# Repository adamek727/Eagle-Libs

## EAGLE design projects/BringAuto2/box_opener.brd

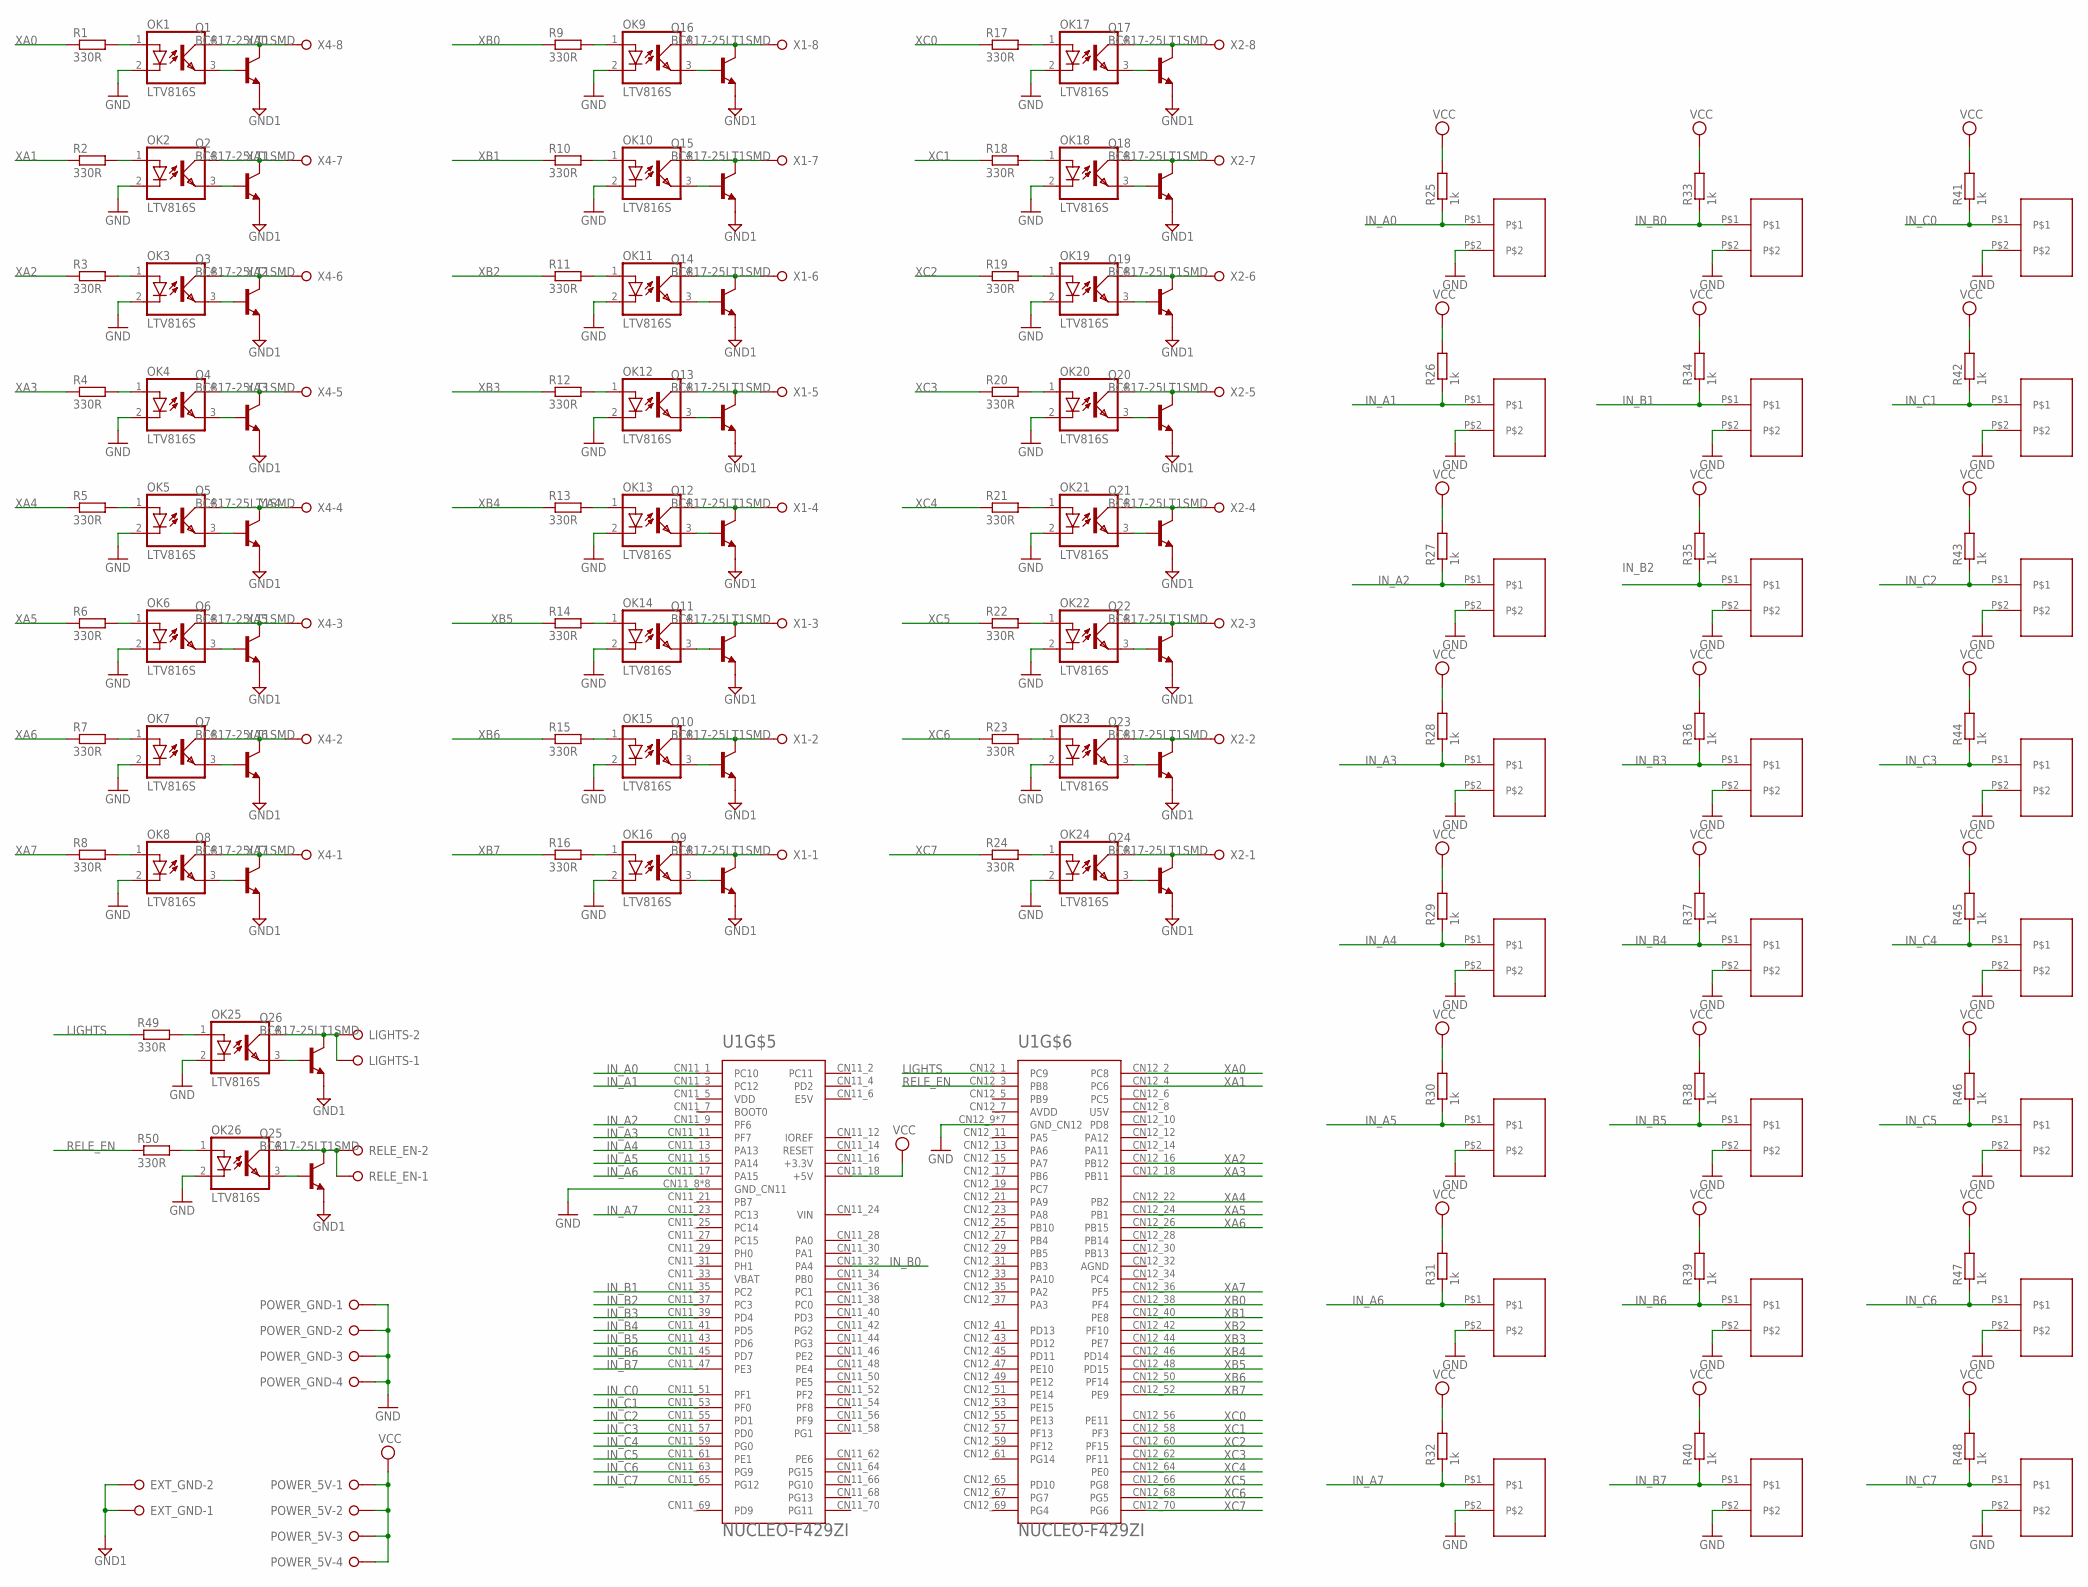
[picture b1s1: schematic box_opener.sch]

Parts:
EXT_GND: W237-02P; W237-132
LIGHTS: W237-132
OK1, OK2, OK3, OK4, OK5, OK6, OK7, OK8, OK9, OK10, OK11, OK12, OK13, OK14, OK15, OK16, OK17, OK18, OK19, OK20, OK21, OK22, OK23, OK24, OK25, OK26: LTV816S; DIL4-SMD
POWER_5V: W237-4P
POWER_GND: W237-4P
Q1, Q2, Q3, Q4, Q5, Q6, Q7, Q8, Q9, Q10, Q11, Q12, Q13, Q14, Q15, Q16, Q17, Q18, Q19, Q20, Q21, Q22, Q23, Q24, Q25, Q26: BC817-25LT1SMD; SOT23-BEC
R1, R2, R3, R4, R5, R6, R7, R8, R9, R10, R11, R12, R13, R14, R15, R16, R17, R18, R19, R20, R21, R22, R23, R24, R49, R50: 330R; M1206
R25, R26, R27, R28, R29, R30, R31, R32, R33, R34, R35, R36, R37, R38, R39, R40, R41, R42, R43, R44, R45, R46, R47, R48: 1k; M1206
RELE_EN: W237-132
U1: NUCLEO-F429ZI; MODULE_NUCLEO-F429ZI
U$1, U$2, U$3, U$4, U$5, U$6, U$7, U$8, U$9, U$10, U$11, U$12, U$13, U$14, U$15, U$16, U$17, U$18, U$19, U$20, U$21, U$22, U$23, U$24: PSH04-02
X1, X2, X4: W237-8P

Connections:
GND: OK1.2 (C), OK2.2 (C), OK3.2 (C), OK4.2 (C), OK5.2 (C), OK6.2 (C), OK7.2 (C), OK8.2 (C), OK9.2 (C), OK10.2 (C), OK11.2 (C), OK12.2 (C), OK13.2 (C), OK14.2 (C), OK15.2 (C), OK16.2 (C), OK17.2 (C), OK18.2 (C), OK19.2 (C), OK20.2 (C), OK21.2 (C), OK22.2 (C), OK23.2 (C), OK24.2 (C), OK25.2 (C), OK26.2 (C), POWER_GND.1, POWER_GND.2, POWER_GND.3, POWER_GND.4, U1.CN11_8 (GND_CN11), U1.CN11_19 (GND_CN11), U1.CN11_20 (GND_CN11), U1.CN11_22 (GND_CN11), U1.CN11_49 (GND_CN11), U1.CN11_60 (GND_CN11), U1.CN11_71 (GND_CN11), U1.CN11_72 (GND_CN11), U1.CN12_9 (GND_CN12), U1.CN12_20 (GND_CN12), U1.CN12_39 (GND_CN12), U1.CN12_54 (GND_CN12), U1.CN12_63 (GND_CN12), U1.CN12_71 (GND_CN12), U1.CN12_72 (GND_CN12), U$1.P$2, U$2.P$2, U$3.P$2, U$4.P$2, U$5.P$2, U$6.P$2, U$7.P$2, U$8.P$2, U$9.P$2, U$10.P$2, U$11.P$2, U$12.P$2, U$13.P$2, U$14.P$2, U$15.P$2, U$16.P$2, U$17.P$2, U$18.P$2, U$19.P$2, U$20.P$2, U$21.P$2, U$22.P$2, U$23.P$2, U$24.P$2
GND1: EXT_GND.1, EXT_GND.2, Q1.E, Q2.E, Q3.E, Q4.E, Q5.E, Q6.E, Q7.E, Q8.E, Q9.E, Q10.E, Q11.E, Q12.E, Q13.E, Q14.E, Q15.E, Q16.E, Q17.E, Q18.E, Q19.E, Q20.E, Q21.E, Q22.E, Q23.E, Q24.E, Q25.E, Q26.E
IN_A0: R25.1, U1.CN11_1 (PC10), U$1.P$1
IN_A1: R26.1, U1.CN11_3 (PC12), U$2.P$1
IN_A2: R27.1, U1.CN11_9 (PF6), U$3.P$1
IN_A3: R28.1, U1.CN11_11 (PF7), U$4.P$1
IN_A4: R29.1, U1.CN11_13 (PA13), U$5.P$1
IN_A5: R30.1, U1.CN11_15 (PA14), U$6.P$1
IN_A6: R31.1, U1.CN11_17 (PA15), U$7.P$1
IN_A7: R32.1, U1.CN11_23 (PC13), U$8.P$1
IN_B0: R33.1, U1.CN11_32 (PA4), U$9.P$1
IN_B1: R34.1, U1.CN11_35 (PC2), U$10.P$1
IN_B2: R35.1, U1.CN11_37 (PC3), U$11.P$1
IN_B3: R36.1, U1.CN11_39 (PD4), U$12.P$1
IN_B4: R37.1, U1.CN11_41 (PD5), U$13.P$1
IN_B5: R38.1, U1.CN11_43 (PD6), U$14.P$1
IN_B6: R39.1, U1.CN11_45 (PD7), U$15.P$1
IN_B7: R40.1, U1.CN11_47 (PE3), U$16.P$1
IN_C0: R41.1, U1.CN11_51 (PF1), U$17.P$1
IN_C1: R42.1, U1.CN11_53 (PF0), U$18.P$1
IN_C2: R43.1, U1.CN11_55 (PD1), U$19.P$1
IN_C3: R44.1, U1.CN11_57 (PD0), U$20.P$1
IN_C4: R45.1, U1.CN11_59 (PG0), U$21.P$1
IN_C5: R46.1, U1.CN11_61 (PE1), U$22.P$1
IN_C6: R47.1, U1.CN11_63 (PG9), U$23.P$1
IN_C7: R48.1, U1.CN11_65 (PG12), U$24.P$1
LIGHTS: R49.1, U1.CN12_1 (PC9)
unnamed: OK1.1 (A), R1.2
unnamed: OK9.1 (A), R9.2
unnamed: OK2.1 (A), R2.2
unnamed: OK10.1 (A), R10.2
unnamed: OK11.1 (A), R11.2
unnamed: OK12.1 (A), R12.2
unnamed: OK3.1 (A), R3.2
unnamed: OK13.1 (A), R13.2
unnamed: OK14.1 (A), R14.2
unnamed: OK4.1 (A), R4.2
unnamed: OK15.1 (A), R15.2
unnamed: OK16.1 (A), R16.2
unnamed: OK5.1 (A), R5.2
unnamed: OK17.1 (A), R17.2
unnamed: OK18.1 (A), R18.2
unnamed: OK6.1 (A), R6.2
unnamed: OK19.1 (A), R19.2
unnamed: OK20.1 (A), R20.2
unnamed: OK7.1 (A), R7.2
unnamed: OK21.1 (A), R21.2
unnamed: OK22.1 (A), R22.2
unnamed: OK8.1 (A), R8.2
unnamed: OK23.1 (A), R23.2
unnamed: OK24.1 (A), R24.2
unnamed: OK25.1 (A), R49.2
unnamed: OK26.1 (A), R50.2
unnamed: OK26.4 (COL), Q25.C, RELE_EN.1, RELE_EN.2
unnamed: LIGHTS.1, LIGHTS.2, OK25.4 (COL), Q26.C
unnamed: OK2.3 (EMIT), Q2.B
unnamed: OK1.3 (EMIT), Q1.B
unnamed: OK3.3 (EMIT), Q3.B
unnamed: OK4.3 (EMIT), Q4.B
unnamed: OK16.4 (COL), Q9.C, X1.1
unnamed: OK15.4 (COL), Q10.C, X1.2
unnamed: OK14.4 (COL), Q11.C, X1.3
unnamed: OK13.4 (COL), Q12.C, X1.4
unnamed: OK12.4 (COL), Q13.C, X1.5
unnamed: OK11.4 (COL), Q14.C, X1.6
unnamed: OK10.4 (COL), Q15.C, X1.7
unnamed: OK9.4 (COL), Q16.C, X1.8
unnamed: OK17.4 (COL), Q17.C, X2.8
unnamed: OK18.4 (COL), Q18.C, X2.7
unnamed: OK19.4 (COL), Q19.C, X2.6
unnamed: OK20.4 (COL), Q20.C, X2.5
unnamed: OK21.4 (COL), Q21.C, X2.4
unnamed: OK22.4 (COL), Q22.C, X2.3
unnamed: OK23.4 (COL), Q23.C, X2.2
unnamed: OK24.4 (COL), Q24.C, X2.1
unnamed: OK5.3 (EMIT), Q5.B
unnamed: OK6.3 (EMIT), Q6.B
unnamed: OK7.3 (EMIT), Q7.B
unnamed: OK8.3 (EMIT), Q8.B
unnamed: OK16.3 (EMIT), Q9.B
unnamed: OK15.3 (EMIT), Q10.B
unnamed: OK13.3 (EMIT), Q12.B
unnamed: OK14.3 (EMIT), Q11.B
unnamed: OK12.3 (EMIT), Q13.B
unnamed: OK11.3 (EMIT), Q14.B
unnamed: OK10.3 (EMIT), Q15.B
unnamed: OK9.3 (EMIT), Q16.B
unnamed: OK17.3 (EMIT), Q17.B
unnamed: OK18.3 (EMIT), Q18.B
unnamed: OK19.3 (EMIT), Q19.B
unnamed: OK20.3 (EMIT), Q20.B
unnamed: OK21.3 (EMIT), Q21.B
unnamed: OK22.3 (EMIT), Q22.B
unnamed: OK23.3 (EMIT), Q23.B
unnamed: OK24.3 (EMIT), Q24.B
unnamed: OK26.3 (EMIT), Q25.B
unnamed: OK25.3 (EMIT), Q26.B
RELE_EN: R50.1, U1.CN12_3 (PB8)
VCC: POWER_5V.1, POWER_5V.2, POWER_5V.3, POWER_5V.4, R25.2, R26.2, R27.2, R28.2, R29.2, R30.2, R31.2, R32.2, R33.2, R34.2, R35.2, R36.2, R37.2, R38.2, R39.2, R40.2, R41.2, R42.2, R43.2, R44.2, R45.2, R46.2, R47.2, R48.2, U1.CN11_18 (+5V)
XA0: R1.1, U1.CN12_2 (PC8)
XA1: R2.1, U1.CN12_4 (PC6)
XA2: R3.1, U1.CN12_16 (PB12)
XA3: R4.1, U1.CN12_18 (PB11)
XA4: R5.1, U1.CN12_22 (PB2)
XA5: R6.1, U1.CN12_24 (PB1)
XA6: R7.1, U1.CN12_26 (PB15)
XA7: R8.1, U1.CN12_36 (PF5)
XB0: R9.1, U1.CN12_38 (PF4)
XB1: R10.1, U1.CN12_40 (PE8)
XB2: R11.1, U1.CN12_42 (PF10)
XB3: R12.1, U1.CN12_44 (PE7)
XB4: R13.1, U1.CN12_46 (PD14)
XB5: R14.1, U1.CN12_48 (PD15)
XB6: R15.1, U1.CN12_50 (PF14)
XB7: R16.1, U1.CN12_52 (PE9)
XC0: R17.1, U1.CN12_56 (PE11)
XC1: R18.1, U1.CN12_58 (PF3)
XC2: R19.1, U1.CN12_60 (PF15)
XC3: R20.1, U1.CN12_62 (PF11)
XC4: R21.1, U1.CN12_64 (PE0)
XC5: R22.1, U1.CN12_66 (PG8)
XC6: R23.1, U1.CN12_68 (PG5)
XC7: R24.1, U1.CN12_70 (PG6)
YA0: OK1.4 (COL), Q1.C, X4.8
YA1: OK2.4 (COL), Q2.C, X4.7
YA2: OK3.4 (COL), Q3.C, X4.6
YA3: OK4.4 (COL), Q4.C, X4.5
YA4: OK5.4 (COL), Q5.C, X4.4
YA5: OK6.4 (COL), Q6.C, X4.3
YA6: OK7.4 (COL), Q7.C, X4.2
YA7: OK8.4 (COL), Q8.C, X4.1

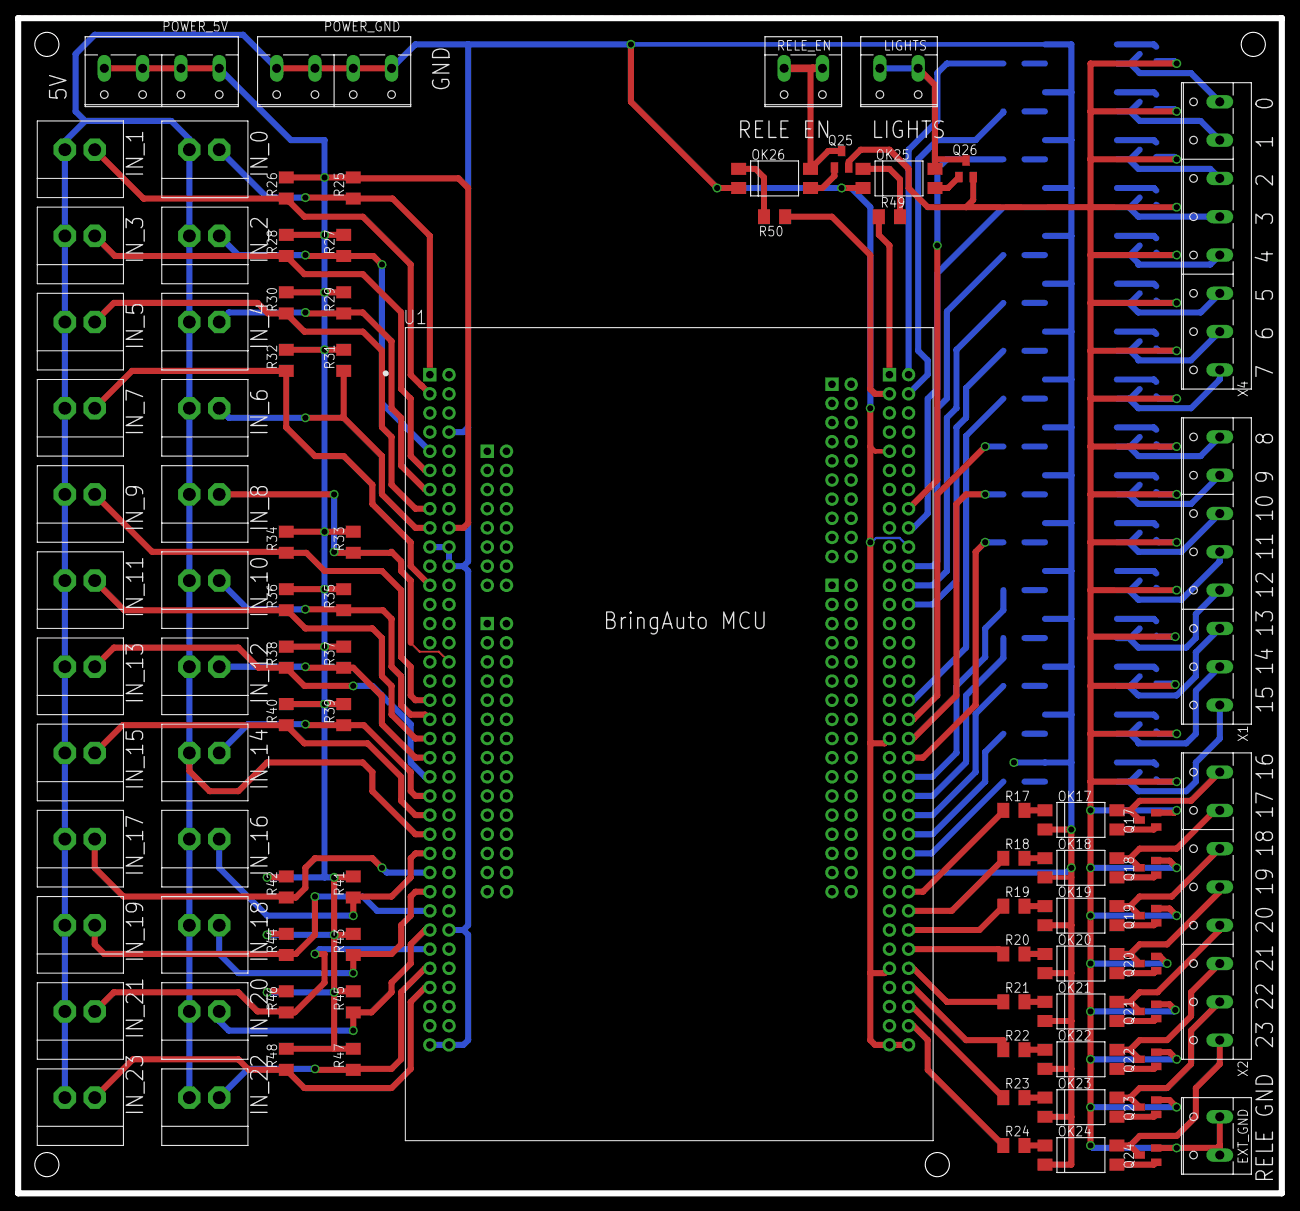
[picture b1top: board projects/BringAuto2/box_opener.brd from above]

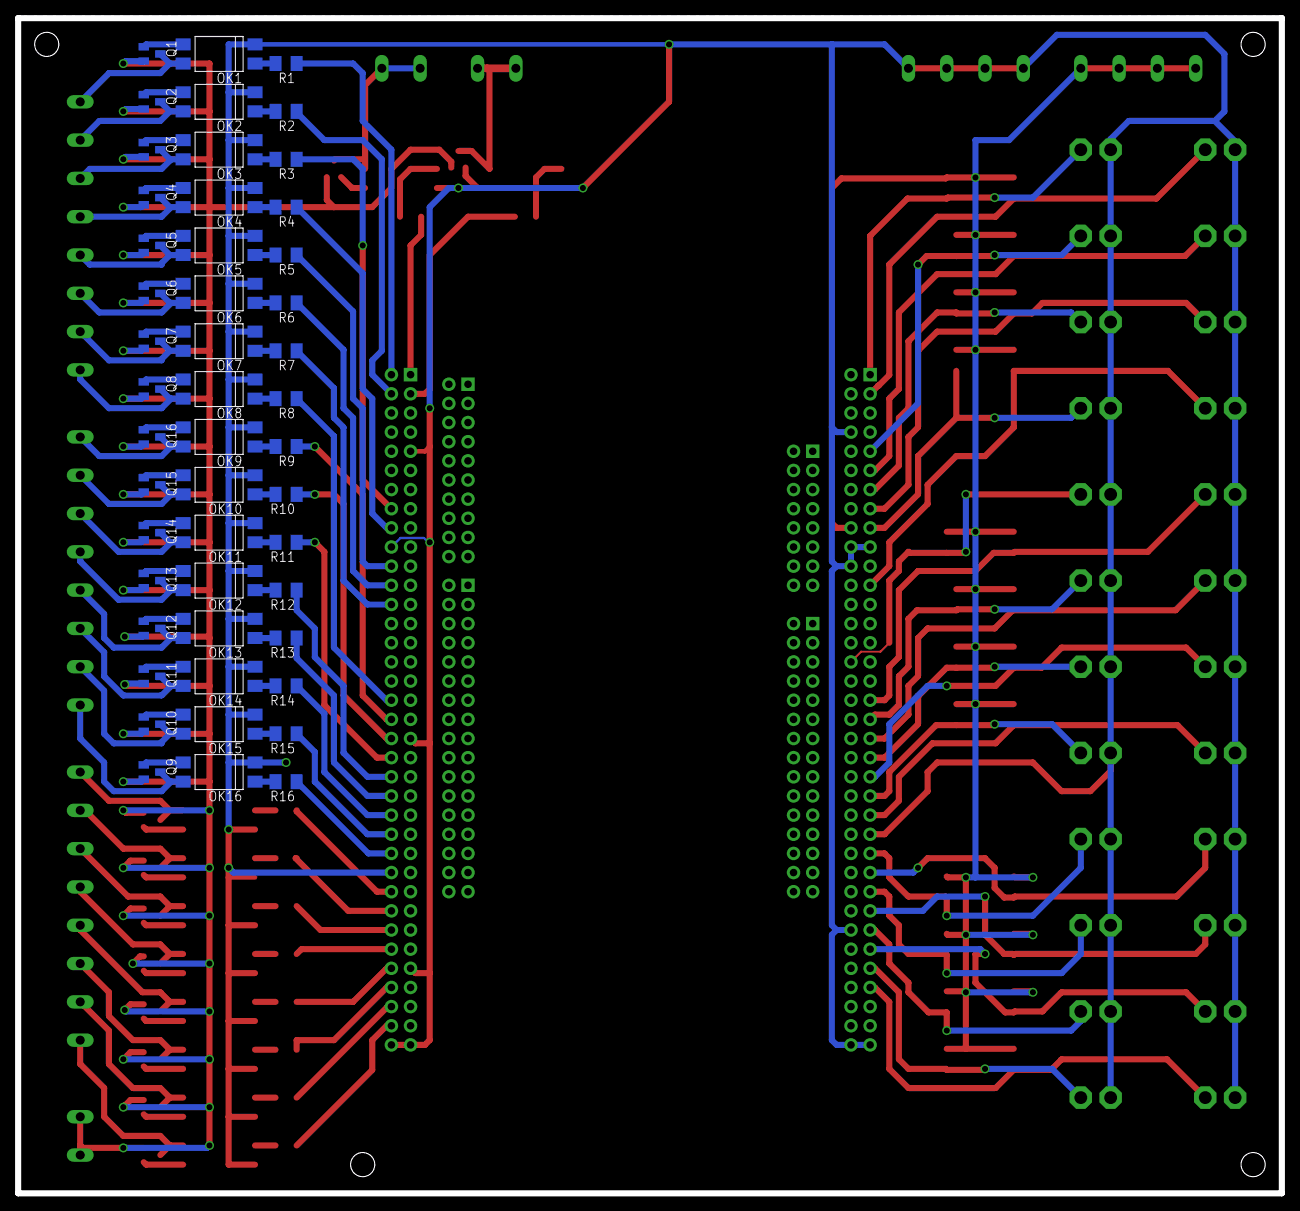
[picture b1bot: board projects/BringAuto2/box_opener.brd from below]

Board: 2 copper layers, 167.6 x 155.9 mm, 135 parts (48 on the bottom side), 131 nets.

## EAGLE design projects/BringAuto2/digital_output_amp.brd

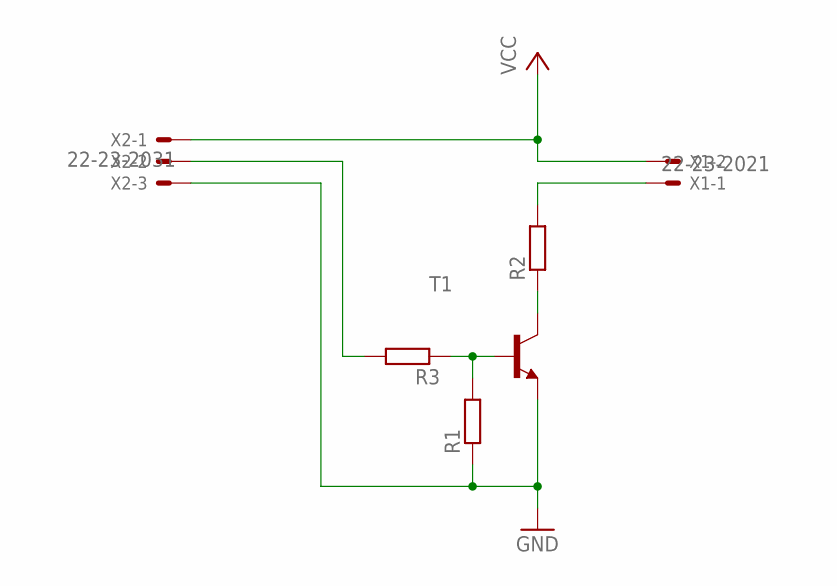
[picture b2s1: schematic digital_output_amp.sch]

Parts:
R1, R2, R3: R-EU_M1206; M1206
T1: BC817-40-NPN-SOT23-BEC; SOT23-BEC
X1: 22-23-2021
X2: 22-23-2031

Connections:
GND: R1.1, T1.E, X2.3
unnamed: R2.2, X1.1
unnamed: R2.1, T1.C
unnamed: R1.2, R3.1, T1.B
unnamed: R3.2, X2.2
VCC: X1.2, X2.1

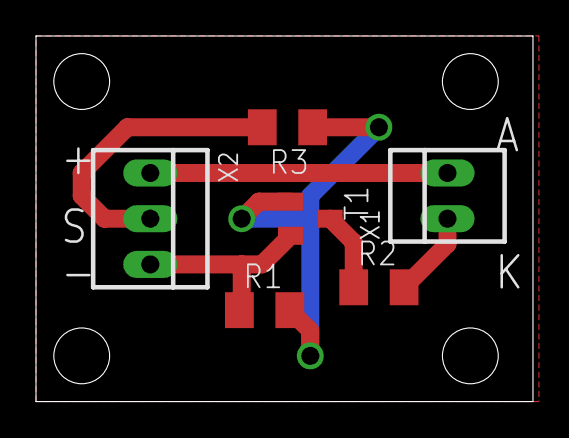
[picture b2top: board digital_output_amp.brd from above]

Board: 2 copper layers, 27.6 x 20.3 mm, 6 parts (0 on the bottom side), 6 nets.

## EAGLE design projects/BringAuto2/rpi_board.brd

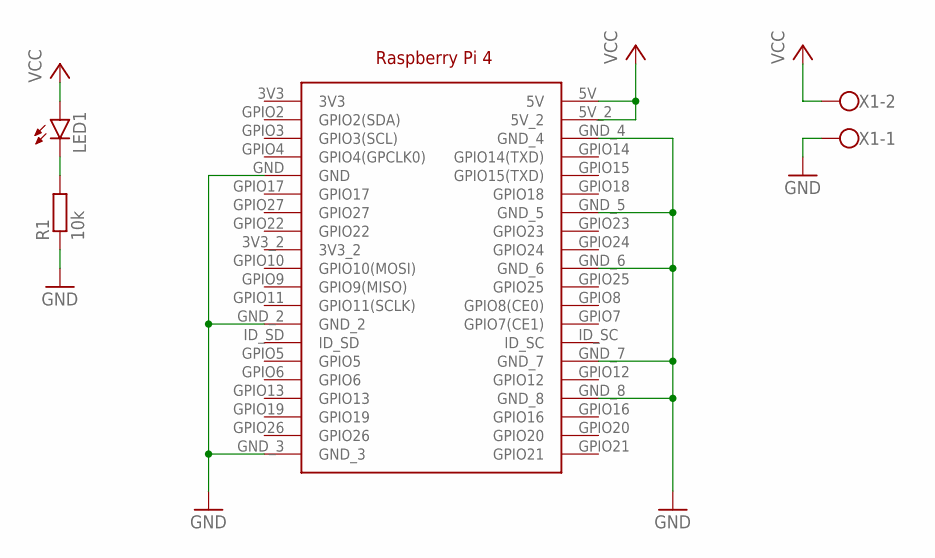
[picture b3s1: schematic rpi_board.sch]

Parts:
LED1: LEDSMT1206; 1206
R1: 10k; M1206
U$1: RPI_4; RPI4_FOOTPRINT
X1: W237-102

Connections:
GND: R1.1, U$1.GND, U$1.GND_2, U$1.GND_3, U$1.GND_4, U$1.GND_5, U$1.GND_6, U$1.GND_7, U$1.GND_8, X1.1
unnamed: LED1.C, R1.2
VCC: LED1.A, U$1.5V, U$1.5V_2, X1.2

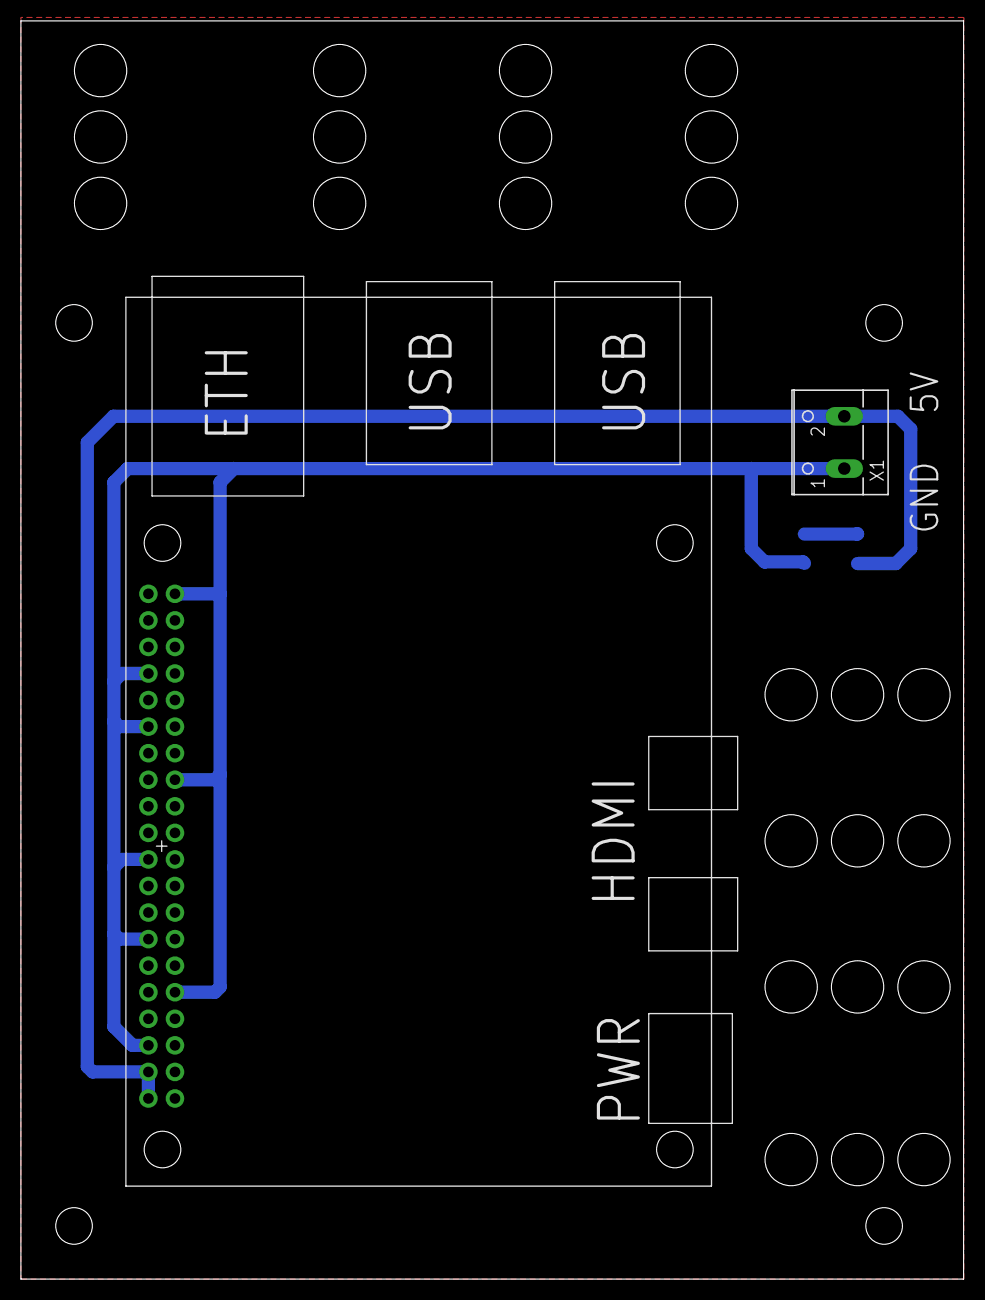
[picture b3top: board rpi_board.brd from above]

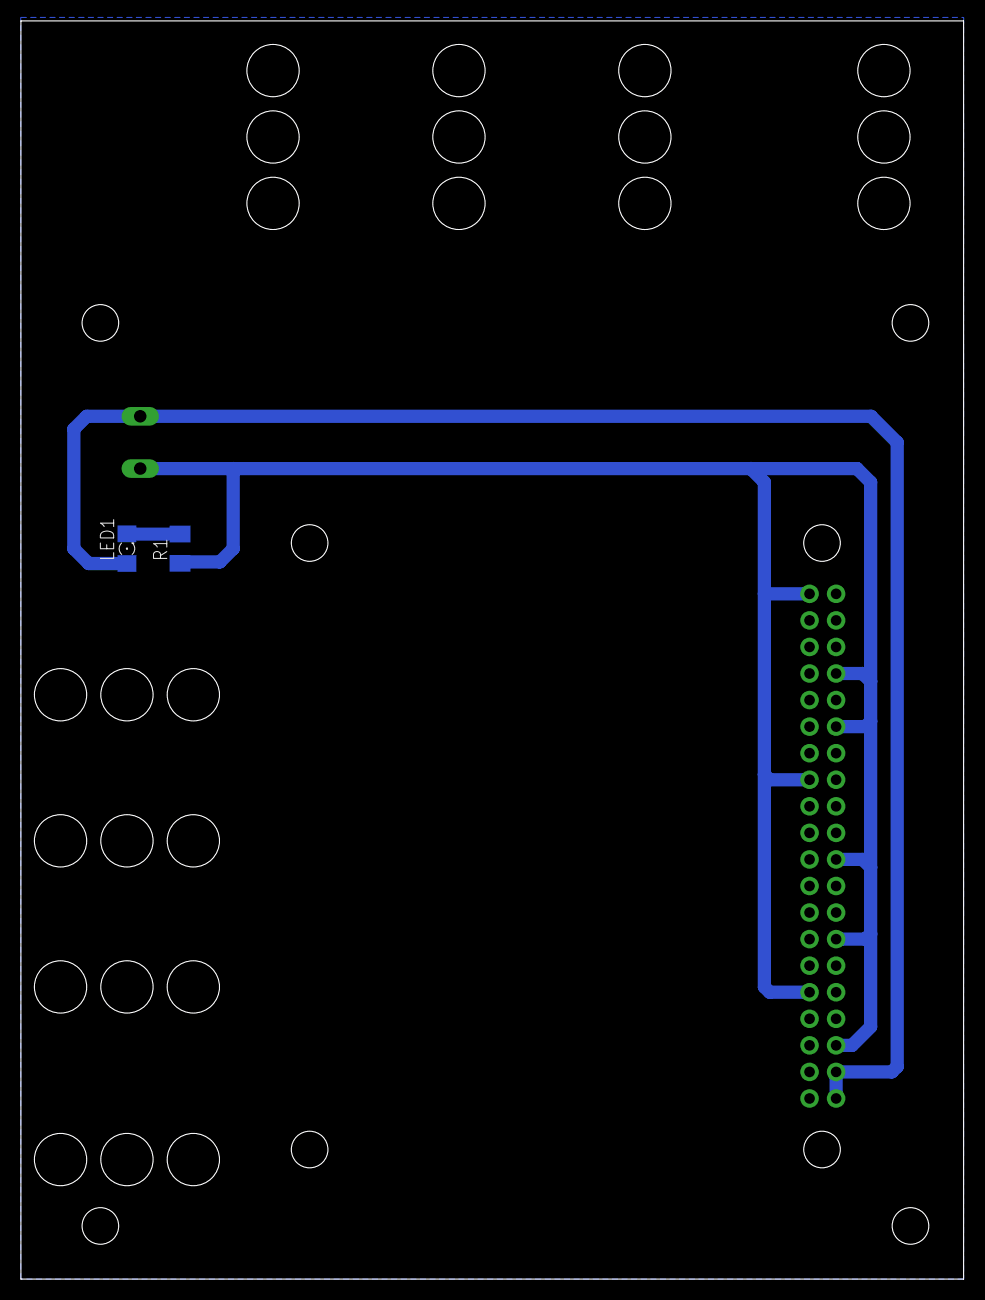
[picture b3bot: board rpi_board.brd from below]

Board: 2 copper layers, 90.2 x 120.3 mm, 4 parts (2 on the bottom side), 3 nets.

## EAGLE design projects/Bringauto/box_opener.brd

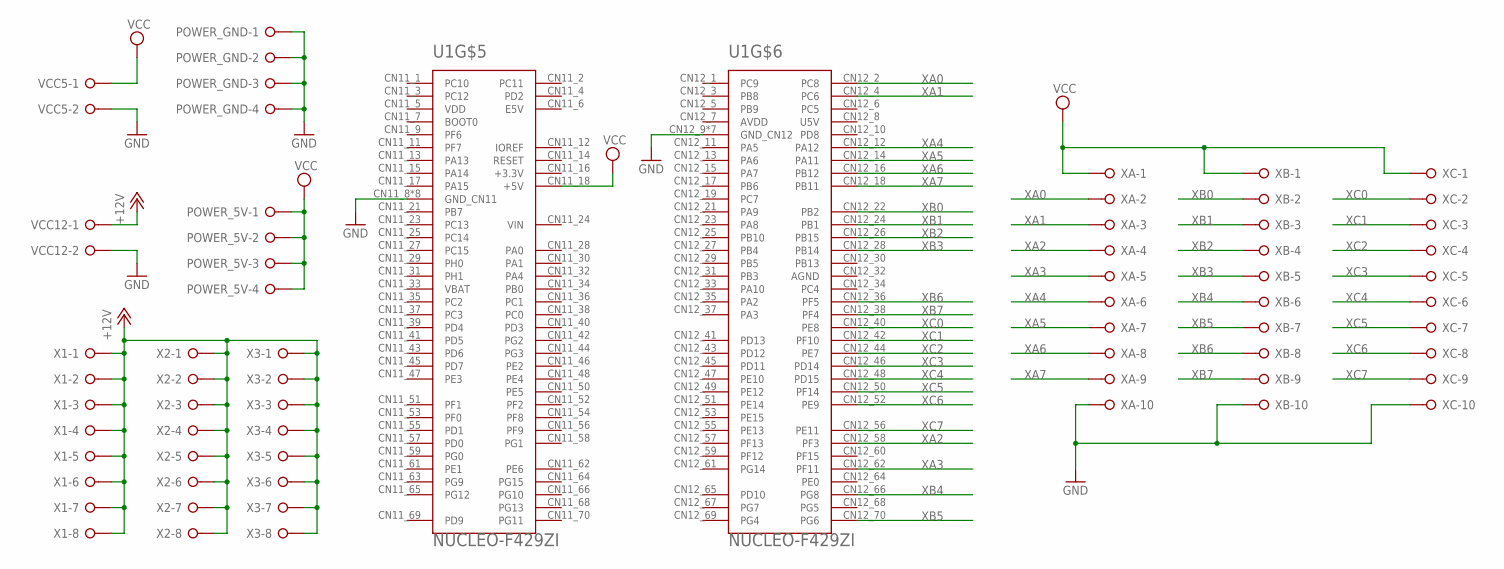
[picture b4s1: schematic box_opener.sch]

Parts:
POWER_5V: W237-4P
POWER_GND: W237-4P
U1: NUCLEO-F429ZI; MODULE_NUCLEO-F429ZI
VCC5, VCC12: W237-132
X1, X2, X3: W237-8P
XA: W237-10P
XB: W237-10P
XC: W237-10P

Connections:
+12V: VCC12.1, X1.1, X1.2, X1.3, X1.4, X1.5, X1.6, X1.7, X1.8, X2.1, X2.2, X2.3, X2.4, X2.5, X2.6, X2.7, X2.8, X3.1, X3.2, X3.3, X3.4, X3.5, X3.6, X3.7, X3.8
GND: POWER_GND.1, POWER_GND.2, POWER_GND.3, POWER_GND.4, U1.CN11_8 (GND_CN11), U1.CN11_19 (GND_CN11), U1.CN11_20 (GND_CN11), U1.CN11_22 (GND_CN11), U1.CN11_49 (GND_CN11), U1.CN11_60 (GND_CN11), U1.CN11_71 (GND_CN11), U1.CN11_72 (GND_CN11), U1.CN12_9 (GND_CN12), U1.CN12_20 (GND_CN12), U1.CN12_39 (GND_CN12), U1.CN12_54 (GND_CN12), U1.CN12_63 (GND_CN12), U1.CN12_71 (GND_CN12), U1.CN12_72 (GND_CN12), VCC5.2, VCC12.2, XA.10, XB.10, XC.10
VCC: POWER_5V.1, POWER_5V.2, POWER_5V.3, POWER_5V.4, U1.CN11_18 (+5V), VCC5.1, XA.1, XB.1, XC.1
XA0: U1.CN12_2 (PC8), XA.2
XA1: U1.CN12_4 (PC6), XA.3
XA2: U1.CN12_58 (PF3), XA.4
XA3: U1.CN12_62 (PF11), XA.5
XA4: U1.CN12_12 (PA12), XA.6
XA5: U1.CN12_14 (PA11), XA.7
XA6: U1.CN12_16 (PB12), XA.8
XA7: U1.CN12_18 (PB11), XA.9
XB0: U1.CN12_22 (PB2), XB.2
XB1: U1.CN12_24 (PB1), XB.3
XB2: U1.CN12_26 (PB15), XB.4
XB3: U1.CN12_28 (PB14), XB.5
XB4: U1.CN12_66 (PG8), XB.6
XB5: U1.CN12_70 (PG6), XB.7
XB6: U1.CN12_36 (PF5), XB.8
XB7: U1.CN12_38 (PF4), XB.9
XC0: U1.CN12_40 (PE8), XC.2
XC1: U1.CN12_42 (PF10), XC.3
XC2: U1.CN12_44 (PE7), XC.4
XC3: U1.CN12_46 (PD14), XC.5
XC4: U1.CN12_48 (PD15), XC.6
XC5: U1.CN12_50 (PF14), XC.7
XC6: U1.CN12_52 (PE9), XC.8
XC7: U1.CN12_56 (PE11), XC.9

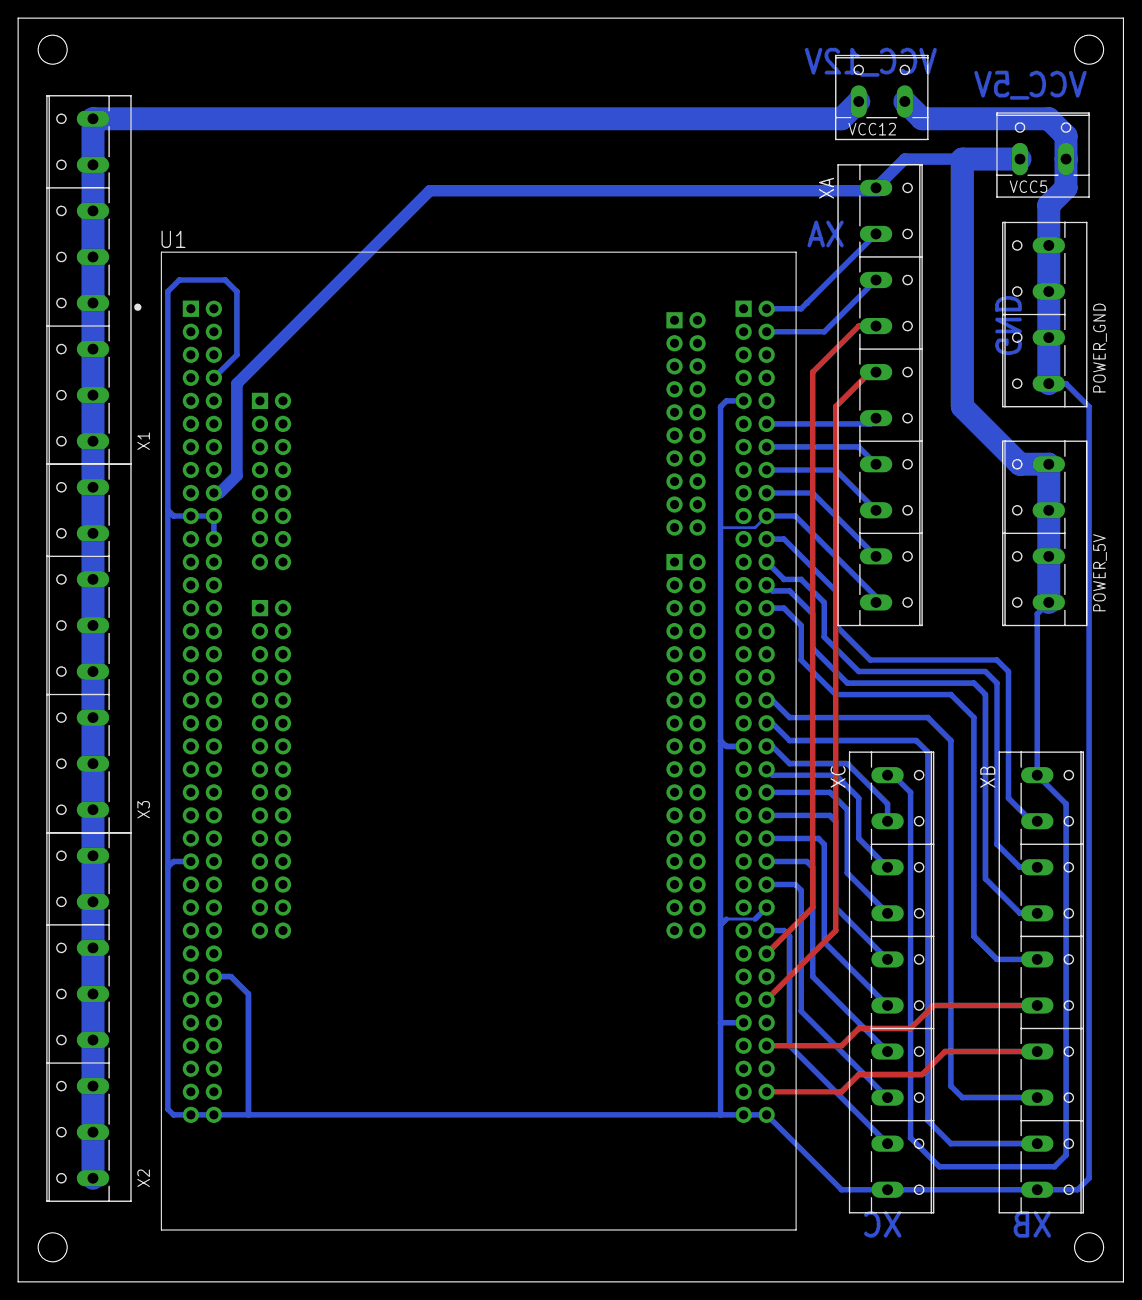
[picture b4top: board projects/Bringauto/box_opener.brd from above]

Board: 2 copper layers, 121.9 x 139.4 mm, 11 parts (0 on the bottom side), 27 nets.

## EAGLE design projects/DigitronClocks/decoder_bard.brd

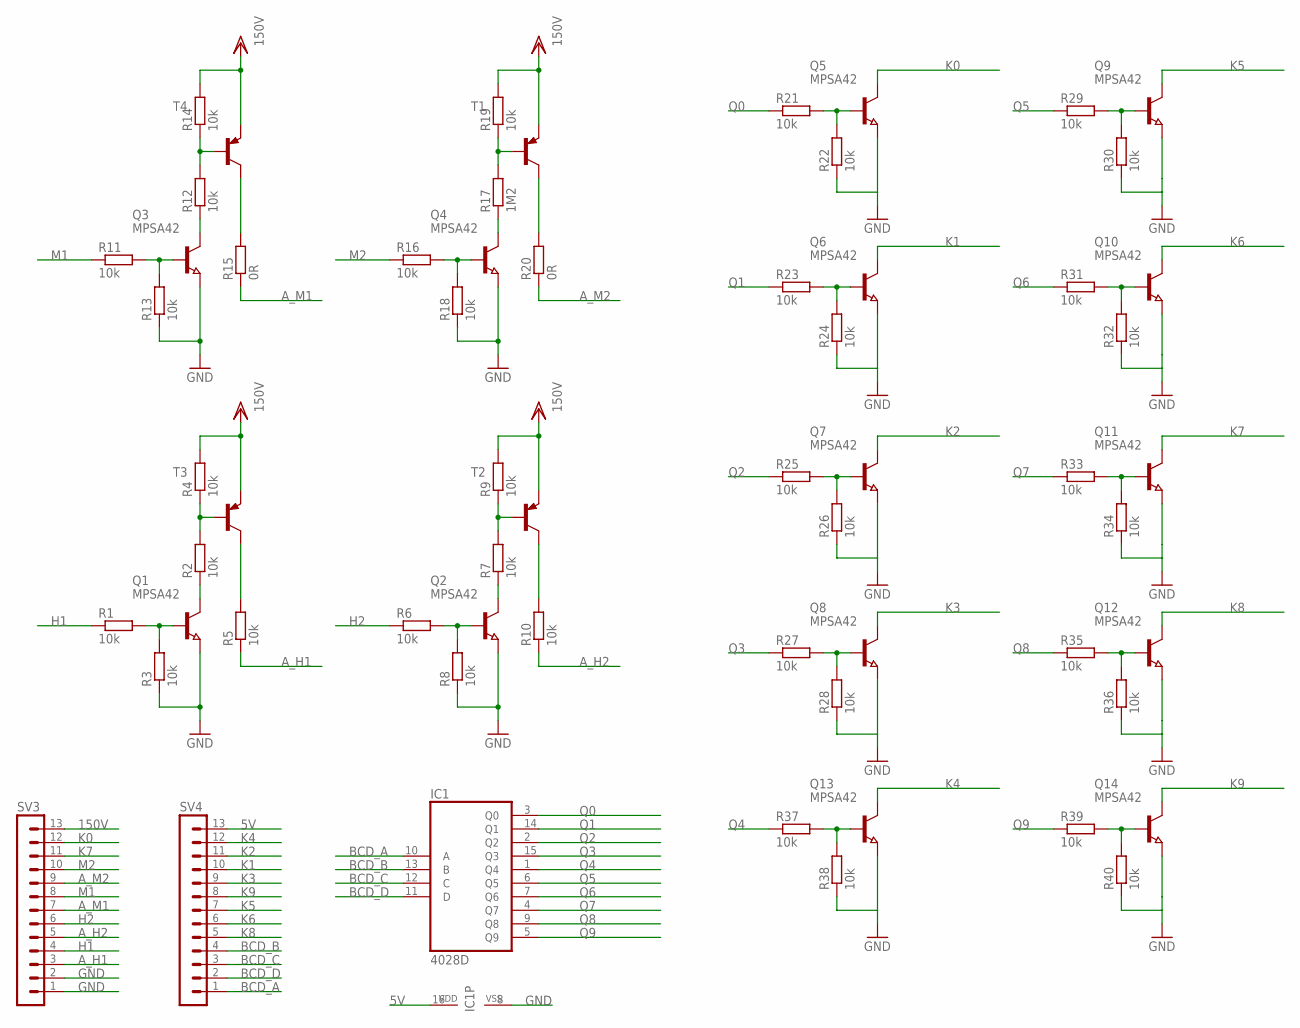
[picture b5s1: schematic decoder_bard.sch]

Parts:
IC1: 4028D; SO16
Q1, Q2, Q3, Q4, Q5, Q6, Q7, Q8, Q9, Q10, Q11, Q12, Q13, Q14: MPSA42; SOT23
R1, R2, R3, R4, R5, R6, R7, R8, R9, R10, R11, R12, R13, R14, R16, R18, R19, R21, R22, R23, R24, R25, R26, R27, R28, R29, R30, R31, R32, R33, R34, R35, R36, R37, R38, R39, R40: 10k; R1206
R15, R20: 0R; R1206
R17: 1M2; R1206
SV3, SV4: MA13-1
T1, T2, T3, T4: MMBTA92LT1-PNP-SOT23-BEC; SOT23-BEC

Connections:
5V: IC1.16 (VDD), SV4.13
150V: R4.2, R9.2, R14.2, R19.2, SV3.13, T1.E, T2.E, T3.E, T4.E
A_H1: R5.1, SV3.3
A_H2: R10.1, SV3.5
A_M1: R15.1, SV3.7
A_M2: R20.1, SV3.9
BCD_A: IC1.10 (A), SV4.1
BCD_B: IC1.13 (B), SV4.4
BCD_C: IC1.12 (C), SV4.3
BCD_D: IC1.11 (D), SV4.2
GND: IC1.8 (VSS), Q1.2 (E), Q2.2 (E), Q3.2 (E), Q4.2 (E), Q5.2 (E), Q6.2 (E), Q7.2 (E), Q8.2 (E), Q9.2 (E), Q10.2 (E), Q11.2 (E), Q12.2 (E), Q13.2 (E), Q14.2 (E), R3.1, R8.1, R13.1, R18.1, R22.1, R24.1, R26.1, R28.1, R30.1, R32.1, R34.1, R36.1, R38.1, R40.1, SV3.1, SV3.2
H1: R1.1, SV3.4
H2: R6.1, SV3.6
K0: Q5.3 (C), SV3.12
K1: Q6.3 (C), SV4.10
K2: Q7.3 (C), SV4.11
K3: Q8.3 (C), SV4.9
K4: Q13.3 (C), SV4.12
K5: Q9.3 (C), SV4.7
K6: Q10.3 (C), SV4.6
K7: Q11.3 (C), SV3.11
K8: Q12.3 (C), SV4.5
K9: Q14.3 (C), SV4.8
M1: R11.1, SV3.8
M2: R16.1, SV3.10
unnamed: Q1.1 (B), R1.2, R3.2
unnamed: Q1.3 (C), R2.1
unnamed: R5.2, T3.C
unnamed: R2.2, R4.1, T3.B
unnamed: Q2.1 (B), R6.2, R8.2
unnamed: Q2.3 (C), R7.1
unnamed: R10.2, T2.C
unnamed: R7.2, R9.1, T2.B
unnamed: Q3.1 (B), R11.2, R13.2
unnamed: Q3.3 (C), R12.1
unnamed: R15.2, T4.C
unnamed: R12.2, R14.1, T4.B
unnamed: Q4.1 (B), R16.2, R18.2
unnamed: Q4.3 (C), R17.1
unnamed: R20.2, T1.C
unnamed: R17.2, R19.1, T1.B
unnamed: Q5.1 (B), R21.2, R22.2
unnamed: Q6.1 (B), R23.2, R24.2
unnamed: Q7.1 (B), R25.2, R26.2
unnamed: Q8.1 (B), R27.2, R28.2
unnamed: Q9.1 (B), R29.2, R30.2
unnamed: Q10.1 (B), R31.2, R32.2
unnamed: Q11.1 (B), R33.2, R34.2
unnamed: Q12.1 (B), R35.2, R36.2
unnamed: Q13.1 (B), R37.2, R38.2
unnamed: Q14.1 (B), R39.2, R40.2
Q0: IC1.3 (Q0), R21.1
Q1: IC1.14 (Q1), R23.1
Q2: IC1.2 (Q2), R25.1
Q3: IC1.15 (Q3), R27.1
Q4: IC1.1 (Q4), R37.1
Q5: IC1.6 (Q5), R29.1
Q6: IC1.7 (Q6), R31.1
Q7: IC1.4 (Q7), R33.1
Q8: IC1.9 (Q8), R35.1
Q9: IC1.5 (Q9), R39.1

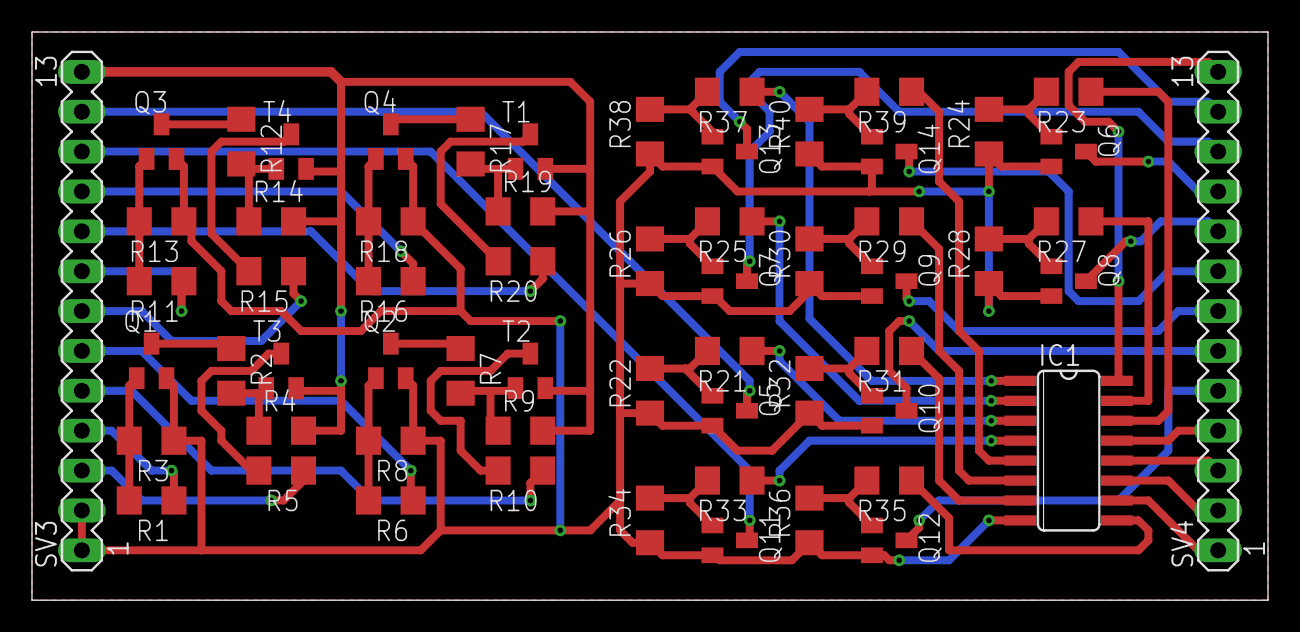
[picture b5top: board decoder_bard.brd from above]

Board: 2 copper layers, 78.7 x 36.2 mm, 61 parts (0 on the bottom side), 61 nets.
